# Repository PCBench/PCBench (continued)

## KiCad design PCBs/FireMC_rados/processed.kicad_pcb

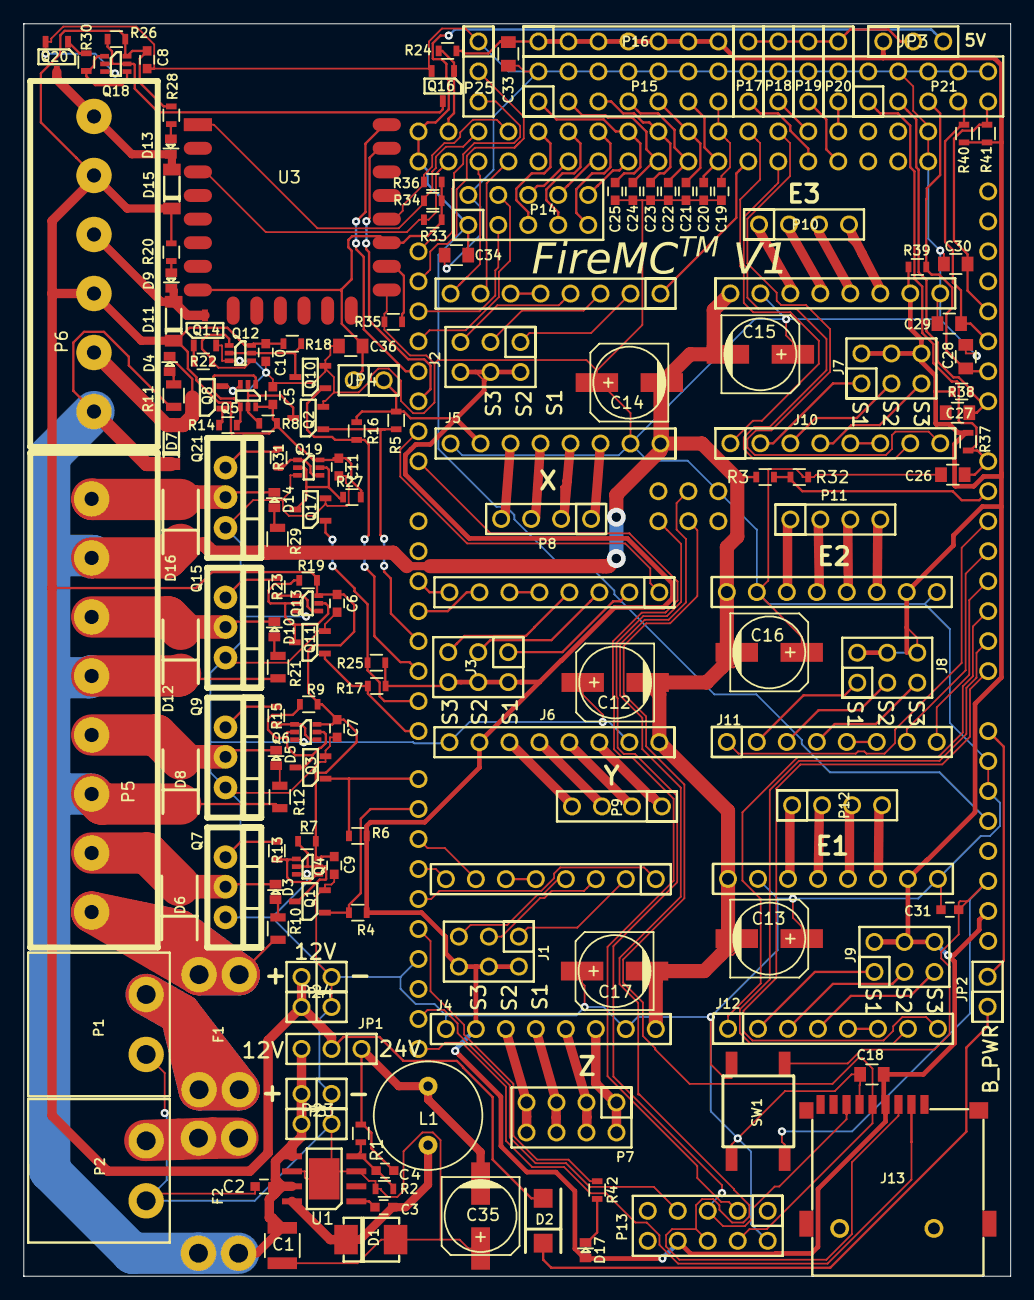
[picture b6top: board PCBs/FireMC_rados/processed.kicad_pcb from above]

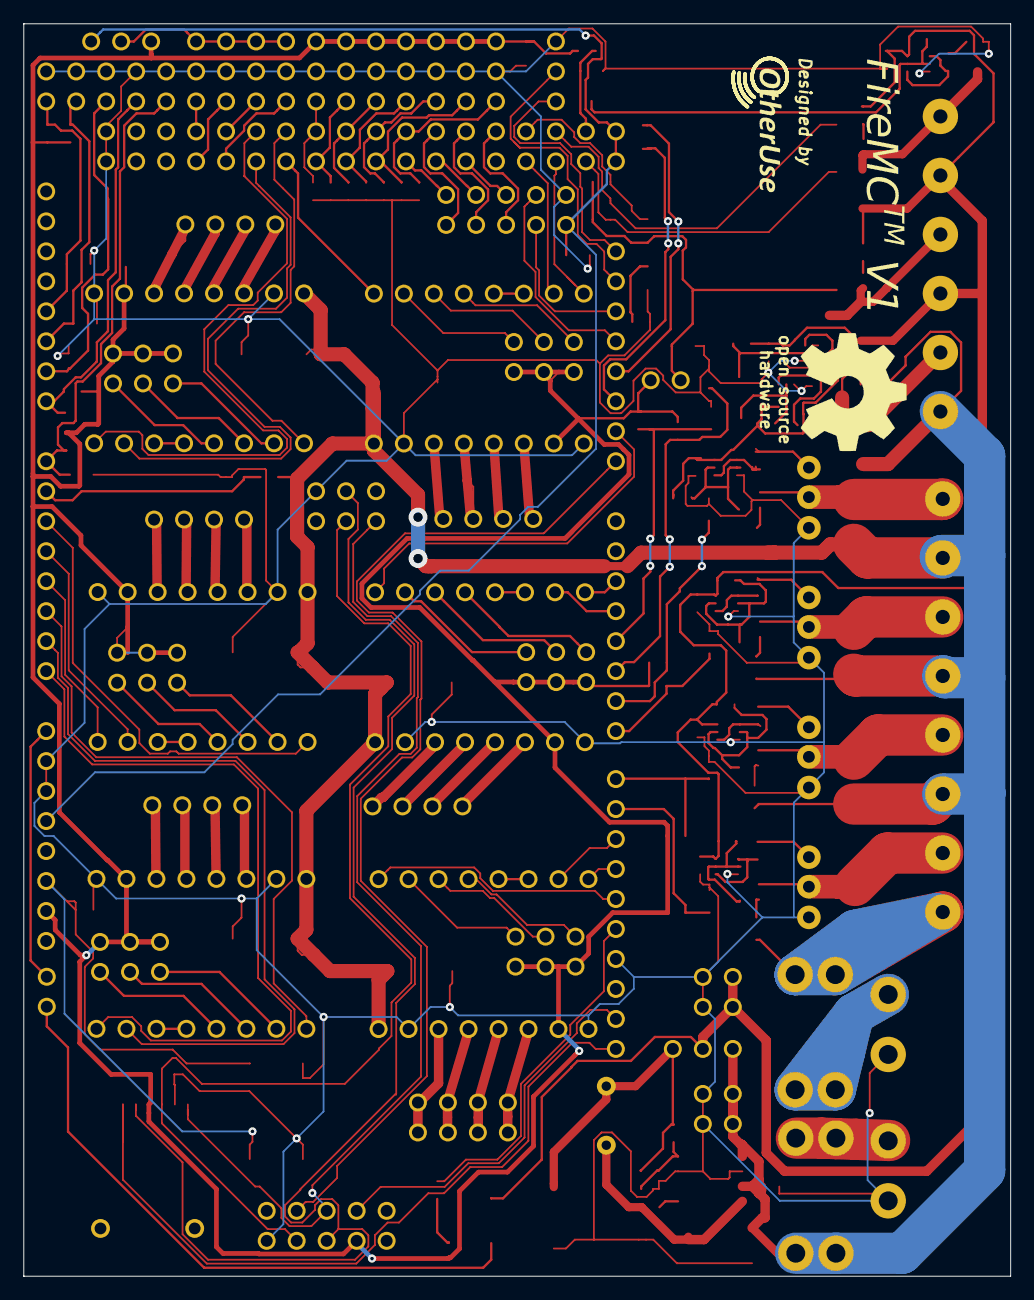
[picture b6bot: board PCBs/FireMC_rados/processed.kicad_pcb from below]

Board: 2 copper layers, 83.6 x 106.1 mm, 166 parts (2 on the bottom side), 166 nets.

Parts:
C1: 4.7uF; C_1210
C2, C3, C19, C20, C21, C22, C23, C24, C25, C31: 100nF; C_0603
C4: DNP; C_0603
C5, C6, C7, C8, C9, C10, C11: 220nF; C_0603
C12, C13, C14, C15, C16, C17: 100uF; c_elec_6.3x7.7
C18, C26, C27, C28, C29, C30, C33, C34, C36: 10uF; C_0805
C35: 33uF; c_elec_6.3x7.7
D1: STPS2L40UF; DO214AA_SMB
D2, D6, D8, D12, D16: ES1G; DO214AC_SMA
D3, D4, D5, D9, D10, D13, D14: RED; LED-0603
D7, D11, D15: 1n4148; DO213AA_SOD-80_MiniMelf
D17: Blue; LED-0603
F1, F2: FUSE; FUSEHOLDER_MINI_KEYSTONE_3557
J1, J2, J3, J7, J8, J9: CONN_02X03; CON_HDR_2x3_2.54mm
J4, J5, J6, J10, J11, J12: STEPSTICK
J13: MICROSD_SLOT_TFP09-2-12B
JP1, JP3: CONN_01X03; CON_HDR_1x3_2.54mm
JP2, JP4: CONN_01X02; CON_HDR_1x2_2.54mm
L1: 18uH; INDUCTOR_BOURNS_RLB914
P1, P2: CONN_01X02; CON_PHOENIX_MSTBA-2.5-2-G-5.08
P3, P4, P23, P24: CONN_01X02; CON_HDR_1x2_2.54mm
P5: TERMINAL_BLOCK; TERMINAL_BLOCK_8_PIN_5mm
P6: TERMINAL_BLOCK; TERMINAL_BLOCK_6_PIN_5mm
P7: CONN_02X04; CON_HDR_2x4_2.54mm
P8, P9, P10, P11, P12: CONN_01X04; CON_HDR_1x4_2.54mm
P13, P14, P21: CONN_02x05; CON_HDR_2x5_2.54mm
P15: CONN_02x07; CON_HDR_2x7_2.54mm
P16: CONN_01X07; CON_HDR_1x7_2.54mm
P17, P18, P19, P20, P25: CONN_01X03; CON_HDR_1x3_2.54mm
Q1, Q2, Q3, Q10, Q11, Q16, Q17: 2N7002P; SOT23_3L
Q4, Q5, Q6, Q12, Q13, Q18, Q19: BC846BPDW1; SC70_6L
Q7, Q9, Q15, Q21: IRFB7545PbF; TO-220-3
Q8, Q14, Q20: SI2318CDS-T1-GE3; SOT23_3L
R1: 620K; R_0603
R2: 68K; R_0603
R3: 22K; R_0603
R4, R5, R6, R16, R17, R24, R25: 100K; R_0603
R7, R8, R9, R18, R19, R26, R27: 2K2; R_0603
R10, R11, R12, R21, R29: 4K7; R_0805
R13, R14, R15, R22, R23, R30, R31: 22R; R_0603
R20, R28: 1K8; R_0603
R32: 2K; R_0603
R33, R34, R35, R36: 10K; R_0603
R37, R38, R39, R40, R41: 4K7; R_0603
R42: 1K; R_0603
SHIELD1: ARDUINO_DUE_SHIELD; ARDUINO_MEGA_DUE_SHIELD_FOOTPRINT_OTH2
SW1: BUTTON; BUTTON_PUSH_SMD_6x6mm
U1: ST1S14PHR; HSOP8
U3: ESP-12E
svg2mod: G***; OtherUseLogo_medium
svg2mod_2, svg2mod_3: G***; firemc-logo

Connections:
+3V3: C18.1, C33.1, D17.1, J1.2, J1.4, J1.6, J2.2, J2.4, J2.6, J3.2, J3.4, J3.6, J4.10, J5.10, J6.10, J7.2, J7.4, J7.6, J8.2, J8.4, J8.6, J9.2, J9.4, J9.6, J10.10, J11.10, J12.10, J13.4, JP3.1, JP4.1, P13.8, P16.1, P16.2, P16.3, P16.4, P16.5, P16.6, P16.7, R4.2, R5.2, R6.2, R16.2, R17.2, R24.2, R25.2, R37.1, R38.1, R39.1, R40.1, R41.1, SHIELD1.IORF
+5V: C34.1, JP3.3, P14.1, SHIELD1.5V, SHIELD1.5V_4, SHIELD1.5V_5
+12V: C5.1, C6.1, C7.1, C8.1, C9.1, C10.1, C11.1, D2.2, D11.2, D15.2, JP1.2, P4.2, P6.3, P6.5, P24.2, Q4.6, Q5.6, Q6.6, Q12.6, Q13.6, Q18.6, Q19.6, R7.2, R8.2, R9.2, R18.2, R19.2, R20.1, R26.2, R27.2, R28.1
ARDUINO-VIN: JP2.2, SHIELD1.V_IN
AUX-1: P17.3, SHIELD1.46
AUX-2: P18.3, SHIELD1.47
AUX-3: P19.3, SHIELD1.48
AUX-4: P20.3, SHIELD1.49
E1-DIR: J12.8, SHIELD1.AD0
E1-EN: J12.1, SHIELD1.AD2
E1-STEP: J12.7, SHIELD1.AD1
E2-DIR: J11.8, SHIELD1.AD3
E2-EN: J11.1, SHIELD1.AD5
E2-STEP: J11.7, SHIELD1.AD4
E3-DIR: J10.8, SHIELD1.45
E3-EN: J10.1, SHIELD1.43
E3-STEP: J10.7, SHIELD1.44
ENC-A: P14.3, SHIELD1.19
ENC-B: P14.4, SHIELD1.18
ENC-SW: P13.7, SHIELD1.SDA1
ESP-PD: R33.2, SHIELD1.22, U3.3
ESP-PROG: R36.2, SHIELD1.27, U3.18
ESP-RST: R34.2, SHIELD1.25, U3.1
ESP-RX: SHIELD1.16, U3.21
ESP-TX: SHIELD1.17, U3.22
GND: C1.2, C2.2, C5.2, C6.2, C7.2, C8.2, C9.2, C10.2, C11.2, C12.2, C13.2, C14.2, C15.2, C16.2, C17.2, C18.2, C19.2, C20.2, C21.2, C22.2, C23.2, C24.2, C25.2, C26.2, C28.2, C29.2, C30.2, C31.2, C33.2, C34.2, C35.2, C36.2, D1.2, J4.9, J4.15, J5.9, J5.15, J6.9, J6.15, J10.9, J10.15, J11.9, J11.15, J12.9, J12.15, J13.6, P1.1, P2.1, P3.1, P4.1, P13.2, P14.2, P15.2, P15.4, P15.6, P15.8, P15.10, P15.12, P15.14, P17.2, P18.2, P19.2, P20.2, P21.2, P21.4, P21.6, P21.8, P21.10, P23.1, P24.1, P25.1, Q1.2, Q2.2, Q3.2, Q4.3, Q5.3, Q6.3, Q7.3, Q8.2, Q9.3, Q10.2, Q11.2, Q12.3, Q13.3, Q14.2, Q15.3, Q16.2, Q17.2, Q18.3, Q19.3, Q20.2, Q21.3, R2.2, R32.2, R35.2, SHIELD1.GND, SHIELD1.GND4, SHIELD1.GND5, SHIELD1.GND6, SW1.2, U1.3, U1.6, U1.9, U3.15
HB-FET: Q1.1, R4.1, SHIELD1.9
HB-OUT: D3.2, D6.2, P5.2, Q7.2
HP-FET1: Q3.1, R6.1, SHIELD1.8
HP-FET2: Q11.1, R17.1, SHIELD1.7
HP-FET3: Q17.1, R25.1, SHIELD1.6
HP-OUT1: D5.2, D8.2, P5.4, Q9.2
HP-OUT2: D10.2, D12.2, P5.6, Q15.2
HP-OUT3: D14.2, D16.2, P5.8, Q21.2
LCD-D4: P14.10, SHIELD1.34
LCD-D5: P14.5, SHIELD1.29
LCD-D6: P14.7, SHIELD1.31
LCD-D7: P14.9, SHIELD1.33
LCD-E: P14.8, SHIELD1.32
LCD-RS: P14.6, SHIELD1.30
LP-FET1: Q10.1, R16.1, SHIELD1.5
LP-FET2: Q16.1, R24.1, SHIELD1.23
LP-OUT1: D9.2, D11.1, P6.4, Q14.3
LP-OUT2: D13.2, D15.1, P6.6, Q20.3
MEASURE-VSUPPLY: R3.2, R32.1, SHIELD1.AD6
MP-FET1: Q2.1, R5.1, SHIELD1.4
MP-OUT1: D4.2, D7.1, P6.2, Q8.3
unnamed: C3.1, D1.1, L1.1, U1.8
unnamed: C3.2, U1.1
unnamed: C4.2, R1.2, R2.1, U1.4
unnamed: C4.1, C35.1, JP1.1, L1.2, R1.1
unnamed: D2.1, JP2.1
unnamed: D3.1, R10.2
unnamed: D4.1, R11.2
unnamed: D5.1, R12.2
unnamed: D9.1, R20.2
unnamed: D10.1, R21.2
unnamed: D13.1, R28.2
unnamed: D14.1, R29.2
unnamed: D17.2, R42.1
unnamed: F1.1, P1.2
unnamed: F2.1, P2.2
unnamed: J1.1, J4.2
unnamed: J1.3, J4.3
unnamed: J1.5, J4.4
unnamed: J2.1, J5.2
unnamed: J2.3, J5.3
unnamed: J2.5, J5.4
unnamed: J3.1, J6.2
unnamed: J3.3, J6.3
unnamed: J3.5, J6.4
unnamed: J4.5, J4.6
unnamed: J4.11, P7.7, P7.8
unnamed: J4.12, P7.5, P7.6
unnamed: J4.13, P7.3, P7.4
unnamed: J4.14, P7.1, P7.2
unnamed: J5.5, J5.6
unnamed: J5.11, P8.4
unnamed: J5.12, P8.3
unnamed: J5.13, P8.2
unnamed: J5.14, P8.1
unnamed: J6.5, J6.6
unnamed: J6.11, P9.4
unnamed: J6.12, P9.3
unnamed: J6.13, P9.2
unnamed: J6.14, P9.1
unnamed: J7.1, J10.2
unnamed: J7.3, J10.3
unnamed: J7.5, J10.4
unnamed: J10.5, J10.6
unnamed: J10.11, P10.4
unnamed: J10.12, P10.3
unnamed: J10.13, P10.2
unnamed: J10.14, P10.1
unnamed: J8.1, J11.2
unnamed: J8.3, J11.3
unnamed: J8.5, J11.4
unnamed: J11.5, J11.6
unnamed: J11.11, P11.4
unnamed: J11.12, P11.3
unnamed: J11.13, P11.2
unnamed: J11.14, P11.1
unnamed: J9.1, J12.2
unnamed: J9.3, J12.3
unnamed: J9.5, J12.4
unnamed: J12.5, J12.6
unnamed: J12.11, P12.4
unnamed: J12.12, P12.3
unnamed: J12.13, P12.2
unnamed: J12.14, P12.1
unnamed: JP3.2, P17.1, P18.1, P19.1, P20.1
unnamed: Q1.3, Q4.2, Q4.5, R7.1
unnamed: Q2.3, Q5.2, Q5.5, R8.1
unnamed: Q3.3, Q6.2, Q6.5, R9.1
unnamed: Q4.1, Q4.4, R13.1
unnamed: Q5.1, Q5.4, R14.1
unnamed: Q6.1, Q6.4, R15.1
unnamed: Q7.1, R13.2
unnamed: Q8.1, R14.2
unnamed: Q9.1, R15.2
unnamed: Q10.3, Q12.2, Q12.5, R18.1
unnamed: Q11.3, Q13.2, Q13.5, R19.1
unnamed: Q12.1, Q12.4, R22.1
unnamed: Q13.1, Q13.4, R23.1
unnamed: Q14.1, R22.2
unnamed: Q15.1, R23.2
unnamed: Q16.3, Q18.2, Q18.5, R26.1
unnamed: Q17.3, Q19.2, Q19.5, R27.1
unnamed: Q18.1, Q18.4, R30.1
unnamed: Q19.1, Q19.4, R31.1
unnamed: Q20.1, R30.2
unnamed: Q21.1, R31.2
unnamed: R35.1, U3.16
PROBE: C19.1, P15.13, SHIELD1.41
RESET: C31.1, SHIELD1.RST, SW1.1
SCL1: P25.3, SHIELD1.21
SD2-CS: P13.3, SHIELD1.14
SD-CS: J13.2, SHIELD1.SCL1
SD-MISO: J13.7, P13.5, SHIELD1.MISO
SD-MOSI: J13.3, P13.6, SHIELD1.MOSI
SD-SCK: J13.5, P13.4, SHIELD1.SCK
SDA1: P25.2, SHIELD1.20
STATUS-LED: R42.2, SHIELD1.13
T0: C26.1, P21.1, R37.2, SHIELD1.AD7
T1: C27.1, P21.3, R38.2, SHIELD1.AD8
T2: C28.1, P21.5, R39.2, SHIELD1.AD9
T3: C29.1, P21.7, R40.2, SHIELD1.AD10
T4: C30.1, P21.9, R41.2, SHIELD1.AD11
Vesp: C36.1, JP4.2, R33.1, R34.1, R36.1, U3.8, U3.17
Vheatbed: D6.1, F1.2, P5.1, R10.1
Vsupply: C1.1, C2.1, C12.1, C13.1, C14.1, C15.1, C16.1, C17.1, D7.2, D8.1, D12.1, D16.1, F2.2, J4.16, J5.16, J6.16, J10.16, J11.16, J12.16, JP1.3, P3.2, P5.3, P5.5, P5.7, P6.1, P23.2, R3.1, R11.1, R12.1, R21.1, R29.1, U1.5, U1.7
X+: C24.1, P15.3, SHIELD1.36
X-: C25.1, P15.1, SHIELD1.35
X-DIR: J5.8, SHIELD1.24
X-EN: J5.1, SHIELD1.42
X-STEP: J5.7, SHIELD1.26
Y+: C22.1, P15.7, SHIELD1.38
Y-: C23.1, P15.5, SHIELD1.37
Y-DIR: J6.8, SHIELD1.2
Y-EN: J6.1, SHIELD1.15
Y-STEP: J6.7, SHIELD1.3
Z+: C20.1, P15.11, SHIELD1.40
Z-: C21.1, P15.9, SHIELD1.39
Z-DIR: J4.8, SHIELD1.11
Z-EN: J4.1, SHIELD1.12
Z-STEP: J4.7, SHIELD1.10

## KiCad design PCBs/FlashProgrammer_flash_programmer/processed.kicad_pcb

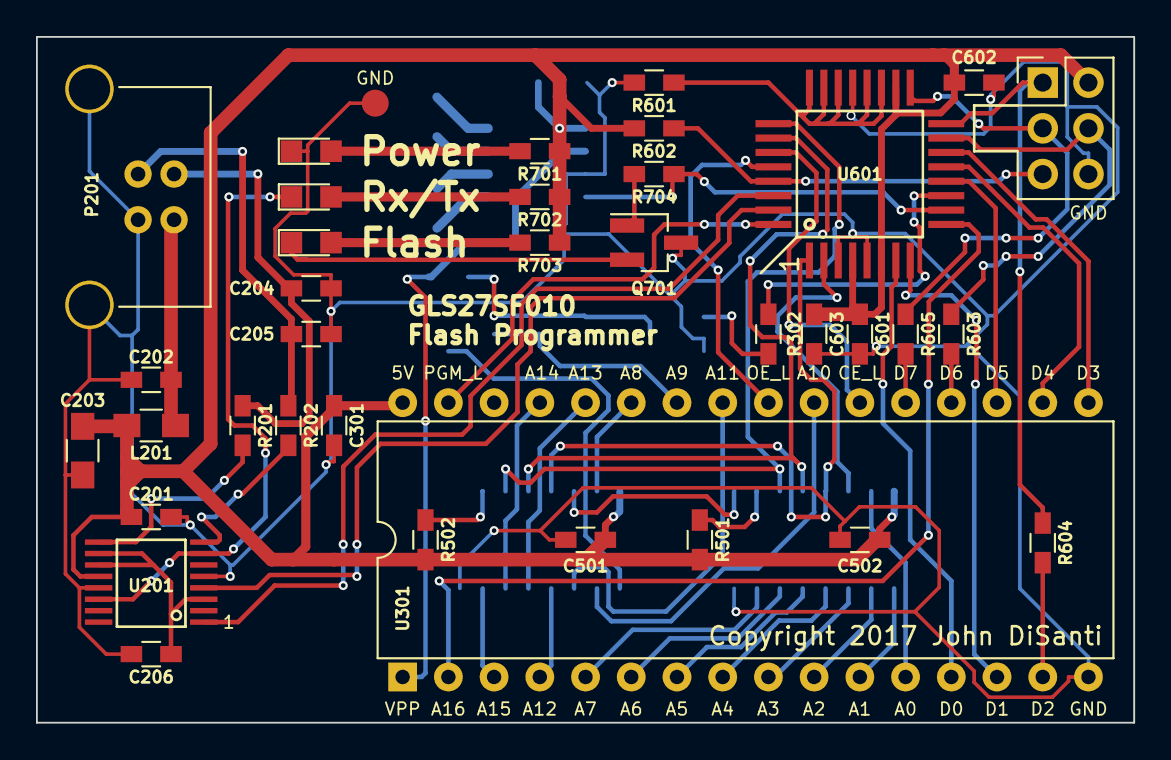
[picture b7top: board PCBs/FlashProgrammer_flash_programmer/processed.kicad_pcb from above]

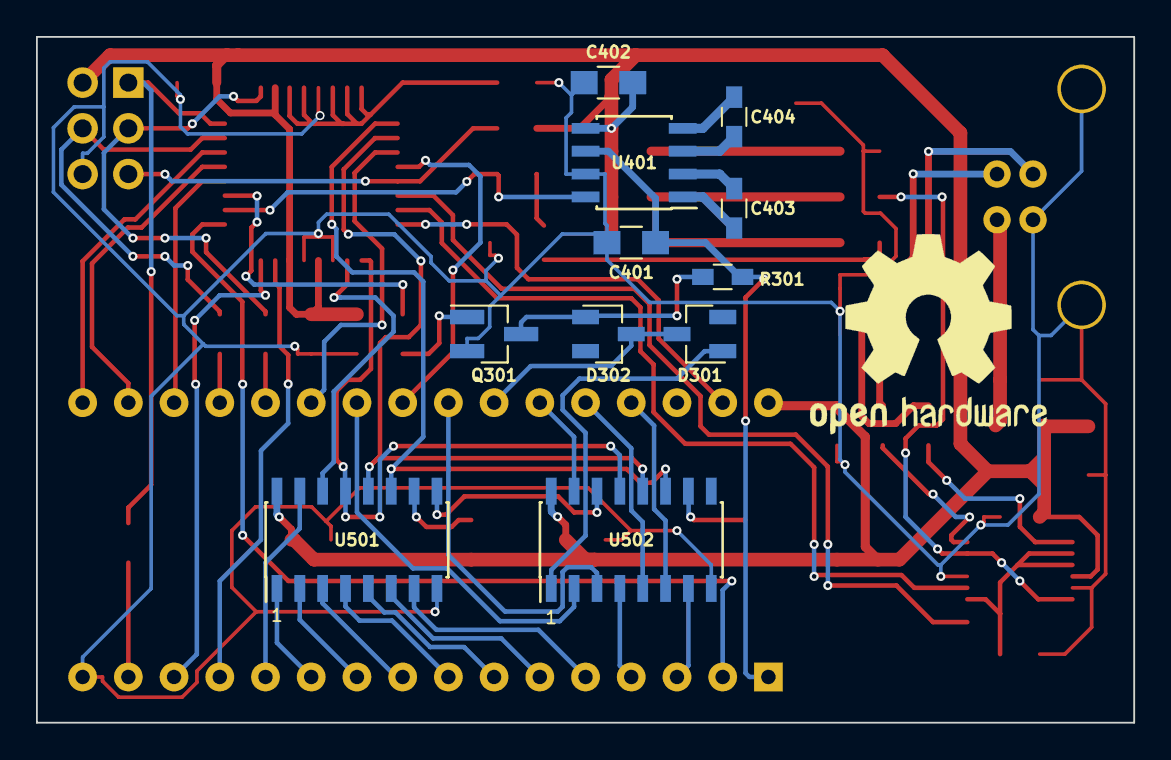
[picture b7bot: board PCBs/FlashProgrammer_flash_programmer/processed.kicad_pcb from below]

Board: 2 copper layers, 61.0 x 38.1 mm, 48 parts (11 on the bottom side), 66 nets.

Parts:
C201, C206, C301, C501, C502, C601, C602, C603: 100nF; R_0603_HandSoldering
C202: 10nF; R_0603_HandSoldering
C203, C401, C402: 4.7uF; R_0805_HandSoldering
C204, C205: 47pF; R_0603_HandSoldering
C403, C404: 22nF; R_0603_HandSoldering
D301, D302: BAT54; D_SOT-23_ANK
D701, D702, D703: LED; LED_0805
GND: Measurement_Point_Round-SMD-Pad_Small
L201: Ferrite_Bead; R_0805_HandSoldering
P201: USB_B
P601: ISP; Pin_Header_Straight_2x03_Pitch2.54mm
Q301: 2N3904; SOT-23_Handsoldering
Q701: 2N3906; SOT-23_Handsoldering
R201, R202: 27; R_0603_HandSoldering
R301: 1k; R_0603_HandSoldering
R302, R501, R502, R602, R704: 10k; R_0603_HandSoldering
R601, R603, R604, R605: 4.7k; R_0603_HandSoldering
R701, R702, R703: 150; R_0603_HandSoldering
U201: FT230X; SSOP-16
U301: GLS27SF010; DIP-32_W15.24mm
U401: MAX662A; SOIC-8_3.9x4.9mm_Pitch1.27mm
U501, U502: 74HC595; SOIC-16_3.9x9.9mm_Pitch1.27mm
U601: ATMEGA328-AU; TQFP-32

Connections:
/12V PSU/VPP_5V_12V: C401.1, R301.1, U301.1, U401.6
/12V PSU/VPP_12V_EN_L: R704.2, U401.8, U601.10
/Address Bus/A0: U301.12, U501.15
/Address Bus/A1: U301.11, U501.1
/Address Bus/A2: U301.10, U501.2
/Address Bus/A3: U301.9, U501.3
/Address Bus/A4: U301.8, U501.4
/Address Bus/A5: U301.7, U501.5
/Address Bus/A6: U301.6, U501.6
/Address Bus/A7: U301.5, U501.7
/Address Bus/A8: U301.27, U502.15
/Address Bus/A9: D301.2, U502.1
/Address Bus/A10: U301.23, U502.2
/Address Bus/A11: U301.25, U502.3
/Address Bus/A12: U301.4, U502.4
/Address Bus/A13: U301.28, U502.5
/Address Bus/A14: U301.29, U502.6
/Address Bus/A15: U301.3, U502.7
/Address Bus/A_OE_L: U501.13, U502.13, U601.1
/Address Bus/A_RCK: U501.12, U502.12, U601.26
/Address Bus/A_SCK: U501.11, U502.11, U601.25
/Address Bus/A_SER: U501.14, U601.2
/Address Bus/A_SER_QH: U501.9, U502.14
/COM1: U201.1, U601.30
/COM2: U201.4, U601.31
/Control/A9_VPP_EN_L: R302.1, U601.11
/Control/A16: U301.2, U601.9
/Control/CE_L: U301.22, U601.27
/Control/D0: U301.13, U601.7
/Control/D1: U301.14, U601.8
/Control/D2: R604.1, U301.15
/Control/D3: U301.17, U601.14
/Control/D4: U301.18, U601.13
/Control/D5: U301.19, U601.12
/Control/D6: R603.1, U301.20
/Control/D7: R605.1, U301.21
/Control/ISP_MISO: P601.1, R604.2, U601.16
/Control/ISP_MOSI: P601.4, R603.2, U601.15
/Control/ISP_RST_L: P601.5, R602.2, U601.29
/Control/ISP_SCK: P601.3, R605.2, U601.17
/Control/OE_L: U301.24, U601.28
/Control/PGM_L: U301.31, U601.32
/Control/UNUSED: R601.2, U601.19, U601.20, U601.22, U601.23, U601.24
/FTDI USB Serial Interface/D+: C205.1, P201.3, R202.2
/FTDI USB Serial Interface/D-: C204.1, P201.2, R201.2
/FTDI USB Serial Interface/RX_TX_L: D702.1, U201.7, U201.14
/FTDI USB Serial Interface/USBDM: R201.1, U201.9
/FTDI USB Serial Interface/USBDP: R202.1, U201.8
/FTDI USB Serial Interface/VBUS: C202.1, L201.2, P201.1
/FTDI USB Serial Interface/VCCIO: C206.2, U201.3, U201.10, U201.11
/Flash ROM/A9_VPP: D301.1, D302.1, U301.26
GND: C201.2, C202.2, C203.2, C204.2, C205.2, C206.1, C301.2, C401.2, C402.1, C501.2, C502.2, C601.2, C602.2, C603.2, D701.1, GND.1, P201.4, P201.5, P601.6, Q301.2, Q701.3, R601.1, U201.5, U201.13, U301.16, U401.7, U501.8, U502.8, U601.3, U601.5, U601.21
unnamed: C403.1, U401.1
unnamed: C403.2, U401.2
unnamed: C404.1, U401.4
unnamed: C404.2, U401.3
unnamed: D302.2, Q301.3, R301.2
unnamed: D701.2, R701.1
unnamed: D702.2, R702.2
unnamed: D703.1, Q701.2
unnamed: D703.2, R703.1
unnamed: Q301.1, R302.2
unnamed: Q701.1, R704.1
unnamed: R501.1, U501.10
unnamed: R502.1, U502.10
VCC: C201.1, C203.1, C301.1, C402.2, C501.1, C502.1, C601.1, C602.1, C603.1, L201.1, P601.2, R501.2, R502.2, R602.1, R701.2, R702.1, R703.2, U201.12, U301.32, U401.5, U501.16, U502.16, U601.4, U601.6, U601.18
